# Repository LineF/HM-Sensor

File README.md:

# HM-Sensor

Nachbau des "Universalsensors" von Dirk, allerdings mit anderen Sensoren.

Zum Einsatz kommen die günstigen DHT-22 und/oder DS18B20 Sensoren. 
Alternativ kann noch ein SHT-21 (sehr kompakt und genau) verwendet werden (Code hierfür allerdings nicht vorhanden)

Der Sensor verwendet als Untermodul die NewAskSin Library von Trilu. Diese habe ich für meine Bedürfnisse etwas angepaßt, wird aber zur Zeit regelmäßig mit Trilus Code aktualisiert.

**Anpassungen:**

 - Erweiterung für WeatherSensor Messages
 - weitere Verbesserungen beim Energieverbrauch
 - Stabilität beim Peering mit HM-CC-RT-DN verbessert
 - Einbau eines 32KHz Uhrenquarzes möglich - damit weitere Verbesserung der Übertragungsgenauigkeit zu einem HM-CC-RT-DN und weitere Reduktion des Stromverbrauchs
 - LED beim Senden kann abgeschaltet werden
 - OSCCAL-Register des Atmel kann remote eingestellt werden (damit kann auch ohne Quarz eine gute Genauigkeit der Taktfrequenz erreicht werden)
 - Automatische Watchdog-Kalibrierung
 - Serielle Debug-Ausgabe auf "flush" umgestellt; damit entfallen die teilweise eingebauten schlecht kalkulierbaren delays
 - Batteriemessgenauigkeit auf 1/100V erhöht (ich mag's halt genau)
 - HAVE_DATA Message-Verarbeitung: damit nimmt der Sensor auch ohne Drücken des Config-Buttons Befehle von der Zentrale bei der nächsten Temperaturübermittlung an
 - der eine oder andere Fix (teilweise von Trilu bereits eingebaut)

Schaltplan, Layout und Belichtungsplan gibt's im Unterordner Schematic.
Die erste Version wurde mit Eagle erstellt (Unterordner Eagle)
Da ich meine Platinen selber ätze, habe ich hier auf doppelseitiges Layout verzichtet - es gibt dafür ein paar Drahtbrücken.

Die zweite Version wurde mit KiCad erstellt und dann bei einem professionellen Fertiger gefertigt (Unterordner Kicad).
Da gibts auch die entsprechenden Bilder.

Achtung:
Die aktuelle Version ab Mitte Mai 2017 hat statt GDO0 jetzt GDO2 verbunden (Fehler beim Erstellen des Schaltplans).
Dies wurde aber im Communication-Modul bei den Parametern IOCFG0 und IOCFG2 entsprechend berücksichtigt.

Als Sendemodul kommt ein CC1101 auf einem günstigen Breakout-Board aus China zum Einsatz.

Entwicklungsumgebung: Atmel Studio 7.0

Der Branch "dev" ist mein aktueller Entwicklungszweig - die Version kann evtl. fehlerhaft oder gar nicht compilierbar sein.
Im Zweifelsfall bitte die Releases verwenden.

Das Release 2.0 ist das letzte stabile und basiert auf der neuen C++ Lib von Trilu (vielen Dank dafür!)

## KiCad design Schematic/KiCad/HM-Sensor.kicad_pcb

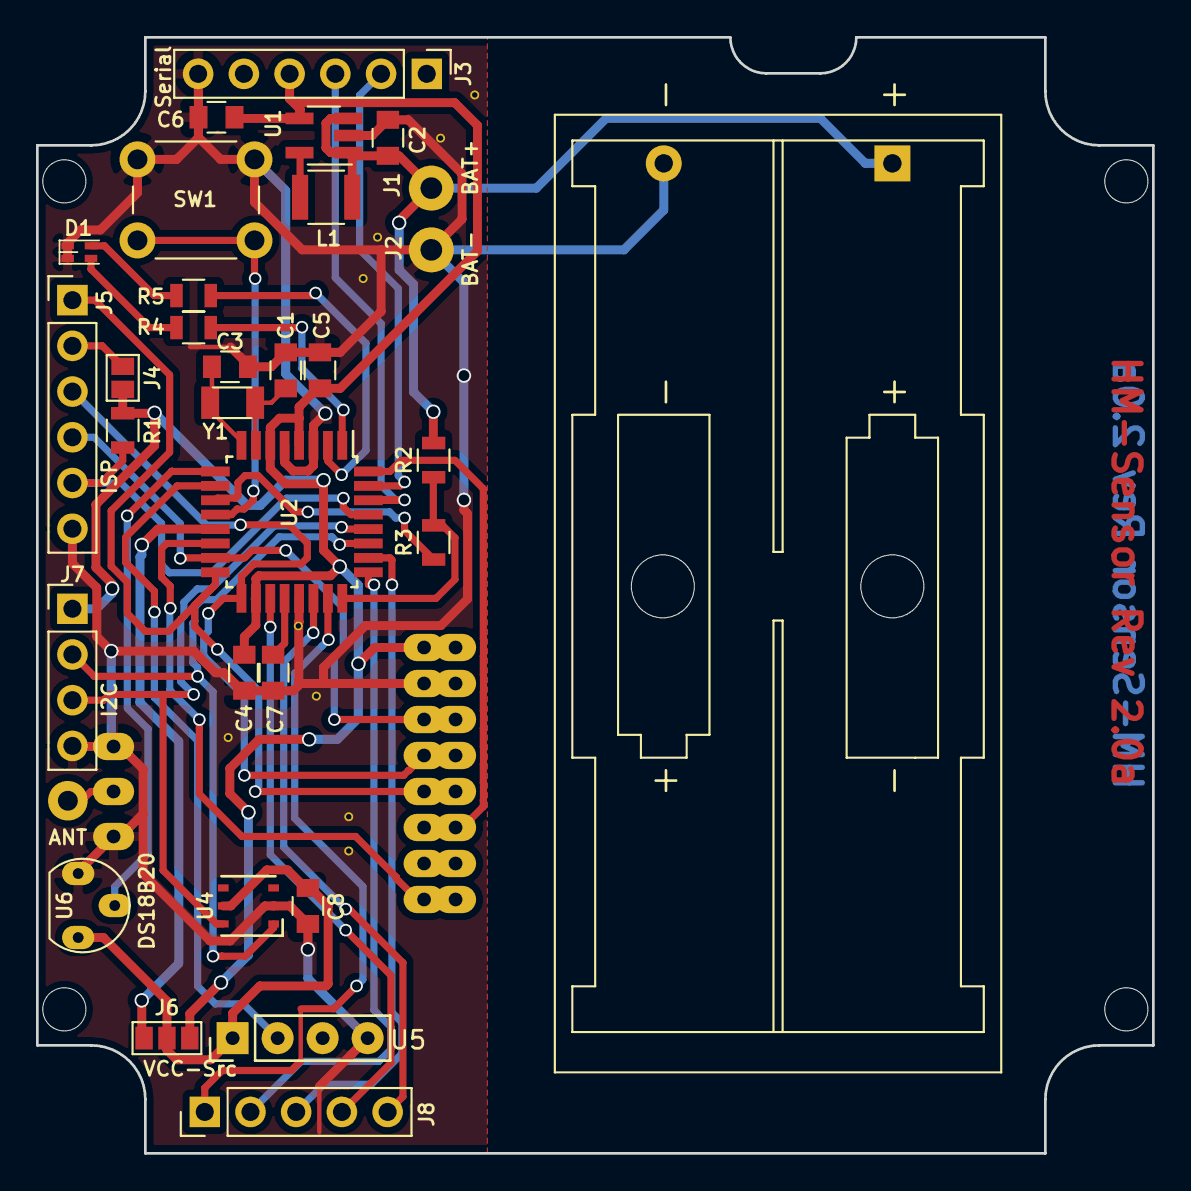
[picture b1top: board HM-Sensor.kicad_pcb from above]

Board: 2 copper layers, 62.0 x 62.0 mm, 37 parts (1 on the bottom side), 35 nets.

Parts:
ANT: SolderWirePad_single_1-2mmDrill
C1, C3: 10pF; C_0805
C2, C6: 10uF; C_0805
C4, C5, C7, C8: 100nF; C_0805
D1: LED_Dual_AACC; LED-Dual-SMD-0603
H1, H2, H3, H4: MountingHole_2.5mm
J1: BAT+; SolderWirePad_single_1-2mmDrill
J2: BAT-; SolderWirePad_single_1-2mmDrill
J3: Serial; Pin_Header_Straight_1x06_Pitch2.54mm
J4: GS2
J5: ISP; Pin_Header_Straight_1x06_Pitch2.54mm
J6: VCC-Src; GS3
J7: I2C; Pin_Header_Straight_1x04_Pitch2.54mm
J8: A0-A7; Pin_Header_Straight_1x05_Pitch2.54mm
L1: 10uH; L_1210
R1: 10k; R_0805
R2: 470k; R_0805
R3: 100k; R_0805
R4, R5: 330; R_0805
REF1: Keystone_2468_2xAAA
SW1: SW_Push; SW_PUSH_6mm_h5mm
U1: MAX1724+; SOT-23-5_HandSoldering
U2: ATMEGA328P-AU; TQFP-32_7x7mm_Pitch0.8mm
U3: CC1101-Modul
U4: SHT2x; SHT21
U5: DHT22; DHT-22
U6: DS18B20; TO-92_Molded_Oval
Y1: 32.768kHz; Crystal_32KHz_CC7V_T1A

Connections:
+3V3: C4.1, C5.1, C6.1, J3.4, J4.2, J6.1, J7.1, R1.1, U1.4, U2.4, U2.6, U2.18, U3.1
//RES: J5.5, R1.2, U2.29
/A0: J8.1, U2.23
/A1: R2.1, R3.2, U2.24
/A2: J8.2, U2.25
/A3: J8.3, U2.26
/A6: J8.4, U2.19
/A7: J8.5, U2.22
/B0: SW1.1, U2.12
/B1: J6.3, U2.13
/B2: U2.14, U3.8
/D2: U2.32, U3.6
/D3: R4.2, U2.1
/D4: R5.2, U2.2
/D5: U2.9, U6.2
/D6: U2.10, U5.2
/D7: R3.1, U2.11
/MISO: J5.1, U2.16, U3.5
/MOSI: J5.4, U2.15, U3.3
/RXD: J3.3, U2.30
/SCK: J5.3, U2.17, U3.4
/SCL: J7.3, U2.28, U4.6
/SDA: J7.2, U2.27, U4.1
/TXD: J3.2, U2.31
/U-BAT: C2.1, J1.1, L1.2, R2.2, REF1.1, U1.1, U1.3
/U-Sens: C8.1, J6.2, U4.5, U5.1, U6.3
/XTAL1: C1.1, U2.7, Y1.2
/XTAL2: C3.1, U2.8, Y1.1
GND: C1.2, C2.2, C3.2, C4.2, C5.2, C6.2, C7.2, C8.2, D1.3, D1.4, J2.1, J3.6, J5.6, J7.4, REF1.2, SW1.2, U1.2, U2.3, U2.5, U2.21, U3.2, U3.9, U3.11, U4.2, U5.4, U6.1
unnamed: ANT.1, U3.10
unnamed: C7.1, U2.20
unnamed: D1.1, R4.1
unnamed: D1.2, R5.1
unnamed: J4.1, J5.2
unnamed: L1.1, U1.5

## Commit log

2016-06-09 adapt fhem config file
2016-06-17 get channel 0 registers running
2016-06-26 added subrepo NewAskSin, fix osccal settings
2016-06-28 more work
2016-07-07 more power savings
2016-07-07 ignore release directory
2016-07-08 use serial_flush
2016-07-08 added atmel studio project files
2016-07-19 more serial flush
2016-07-31 more schematic files added
2016-08-01 change in ee structure due to merge with DevAES fix index changes due to DevAES merge
2016-08-02 some cleanup
2016-08-02 changes due to new merge
2016-08-04 new submodule commit
2016-08-30 changes to get it compiled after merge
2016-09-01 change 8000ms sleep to 250ms sleep
2016-09-18 debug startup
2016-09-30 fix compilation errors
2016-10-01 first working compile with new cmTHSensWeather class
2016-10-06 more
2016-10-06 raise firmware level
2016-10-07 some work, but reading registers doesn't work
2016-10-08 fix minor typos, add extended debug console
2016-10-08 some small debug changes
2016-10-16 new schematic for low freq crystal oscillator and sht21
2016-10-19 modify chnl0 change notification
2016-10-20 new NewAskSin commit
2016-10-29 changes to support low frequency oscillator
2016-10-30 cosmetic changes and go back to TH1 values
2016-10-31 schematic changed - only one crystal load capacitor needed, crystal doc added
2016-10-31 a bit more debugging
2016-11-02 changed readme
2016-11-03 changes after merge
2016-11-03 new submodule id
2016-11-05 revert to 250ms mode
2016-11-28 some corrections
2016-12-05 file set changed
2016-12-26 fix compilation errors due to merge, fix project member files
2016-12-28 debug code now in extra module
2016-12-28 changes for new 32KHz code
2017-01-04 fix 85C and change in filenames
2017-01-14 change in file structure
2017-01-14 code compiling again after merge
2017-01-26 change file structure
2017-01-26 enable burstRX mode again
2017-02-09 some changes
2017-02-12 add configurable cyclicMessageOffset, r/o factory osccal and frequency test led
2017-02-16 change power_modes, change factOscCal handling, change debugging
2017-02-22 changes for new battery oversampling
2017-03-07 pins redefined, change bat measure time
2017-03-16 submodule commit changed
2017-03-28 add free_ram()
2017-03-28 change to refs
2017-04-22 added kicad schematic files
2017-04-22 pcb routing complete
2017-04-23 went to production
2017-04-26 better ground layout
2017-04-26 fix config_status_request
2017-05-11 change hmid and serial for new test device
2017-05-11 restructure schematic file tree, add pictures
